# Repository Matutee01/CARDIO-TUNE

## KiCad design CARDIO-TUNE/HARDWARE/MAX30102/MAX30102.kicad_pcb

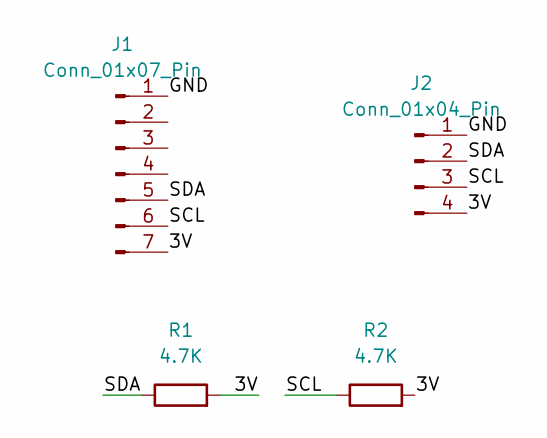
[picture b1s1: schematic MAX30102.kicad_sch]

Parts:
J1: Conn_01x07_Pin; PinSocket_1x07_P2.54mm_Vertical
J2: Conn_01x04_Pin; PinSocket_1x04_P2.54mm_Vertical
R1, R2: 4.7K; R_Axial_DIN0207_L6.3mm_D2.5mm_P7.62mm_Horizontal

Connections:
/3V: J1.7, J2.4, R1.2, R2.2
/GND: J1.1, J2.1
/SCL: J1.6, J2.3, R2.1
/SDA: J1.5, J2.2, R1.1

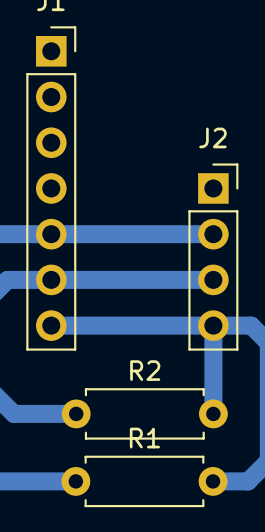
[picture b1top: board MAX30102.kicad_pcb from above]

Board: 2 copper layers, 4 parts (0 on the bottom side), 4 nets.
